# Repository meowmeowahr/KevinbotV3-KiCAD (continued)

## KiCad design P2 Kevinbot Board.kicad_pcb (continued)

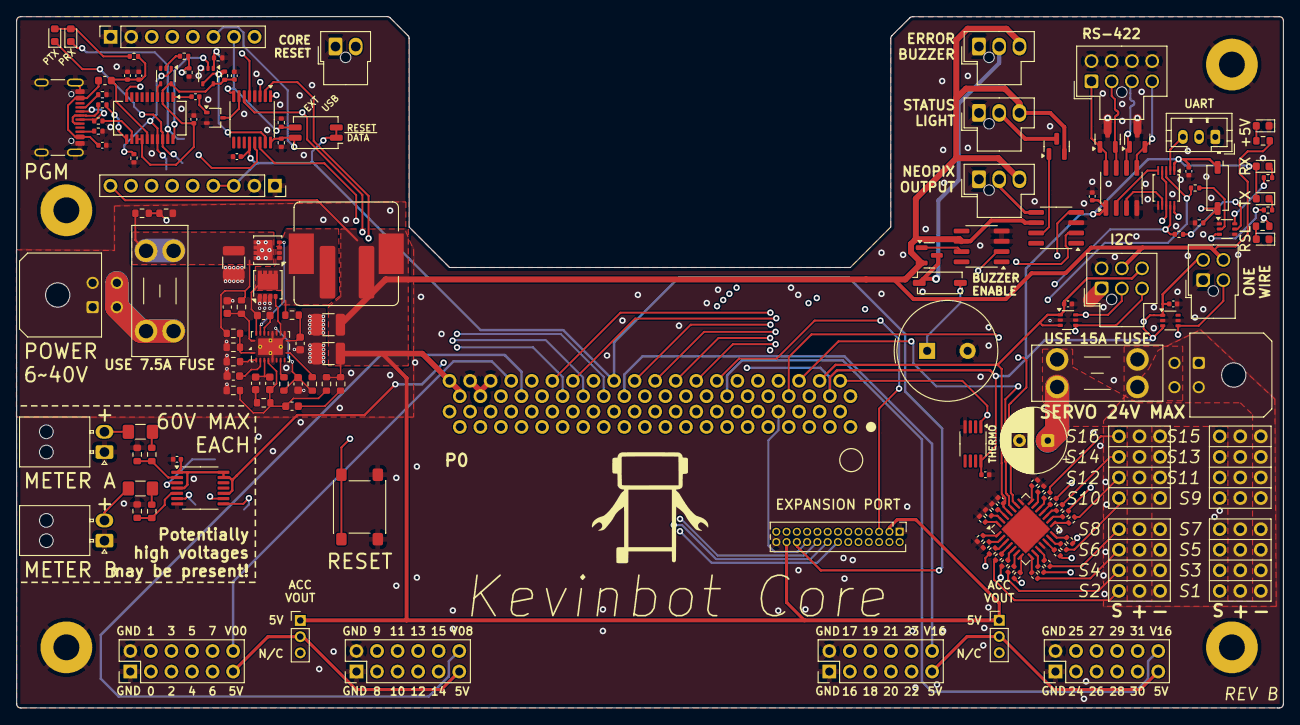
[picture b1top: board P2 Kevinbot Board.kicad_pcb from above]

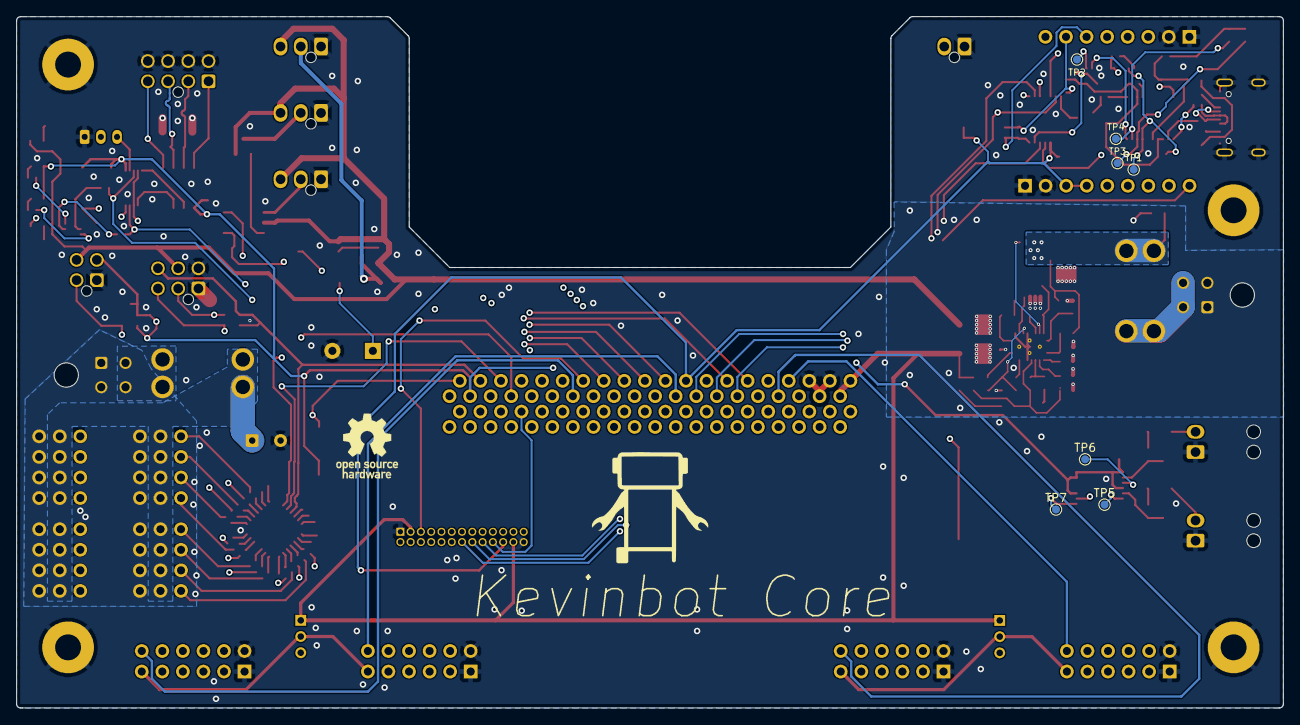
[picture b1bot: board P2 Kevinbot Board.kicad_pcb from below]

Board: 4 copper layers, 156.5 x 85.4 mm, 165 parts (8 on the bottom side), 192 nets.

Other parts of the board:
G1, G2: LOGO; Kevinbot15mm

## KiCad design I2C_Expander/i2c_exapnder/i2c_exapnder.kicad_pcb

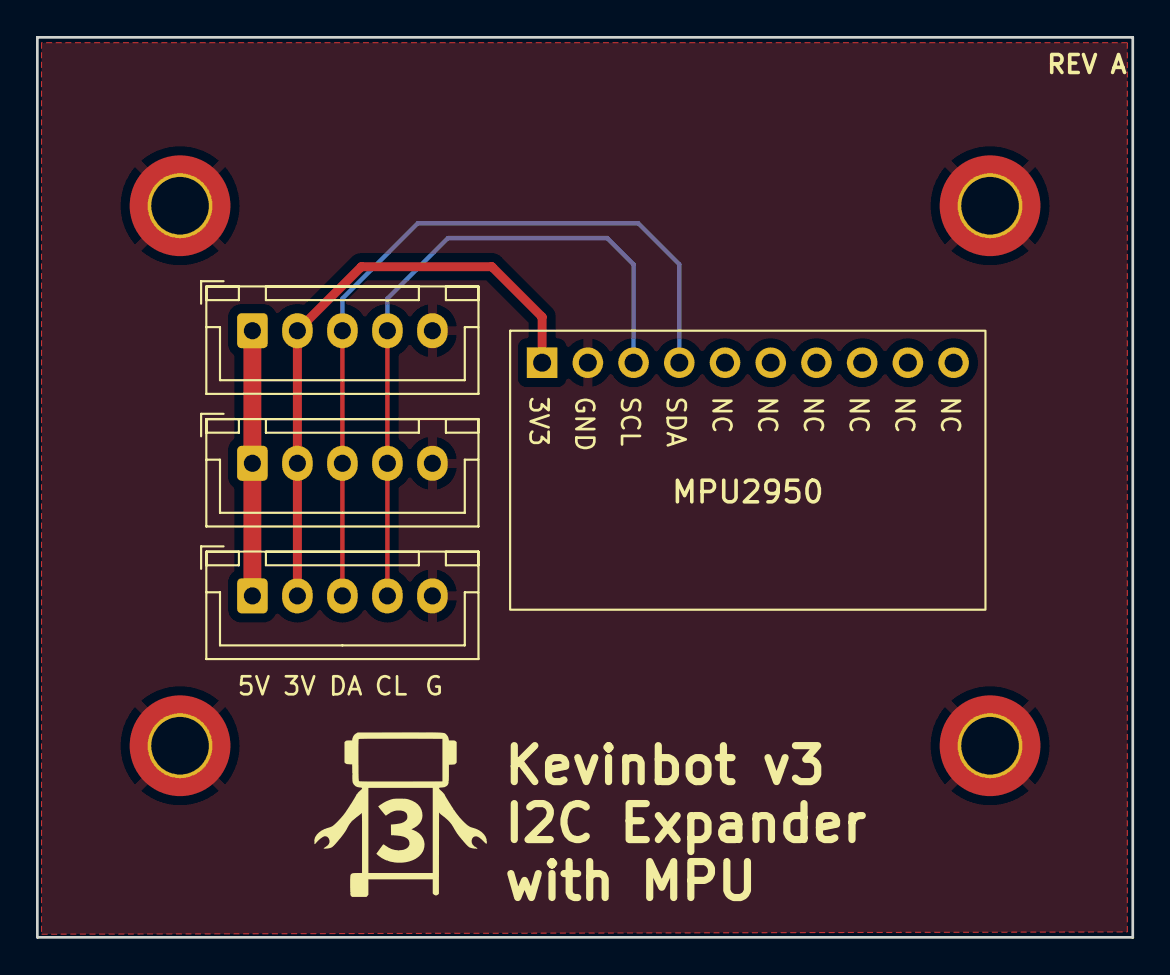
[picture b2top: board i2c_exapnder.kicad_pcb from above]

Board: 2 copper layers, 60.9 x 50.0 mm, 8 parts (0 on the bottom side), 5 nets.

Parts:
H1, H2, H3, H4: MountingHole_Pad; MountingHole_3.2mm_M3_DIN965_Pad_TopBottom
J1: Conn_01x10; MPU2950_Module
J2, J3, J4: Conn_01x05; JST_XH_B5B-XH-A_1x05_P2.50mm_Vertical

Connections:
+5V: J2.1, J3.1, J4.1
GND: H1.1, H2.1, H3.1, H4.1, J1.2, J2.5, J3.5, J4.5
SCL: J1.3, J2.4, J3.4, J4.4
SDA: J1.4, J2.3, J3.3, J4.3
V08: J1.1, J2.2, J3.2, J4.2

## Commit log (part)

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2023-02-17 Board cleanup
2023-02-26 Replace I2C headers with JST
2023-02-26 Fix DRC Warnings
2023-02-26 Move screw holes, move serial port to top
2023-02-26 Update gitignore
2023-02-26 Add I2C Expander with MPU2950
2023-02-26 Add 3D model to power jack
2023-02-26 Update Image
2023-02-27 Align I2C Expander screw holes
2023-02-27 Update Board Settings on I2C Expander
2023-03-06 Add logo and text to I2C Expander
2023-03-06 Add i2c expander image
2023-03-06 Add i2c expander image to README
2023-03-08 Cleanup
2023-05-07 Redesign for SMD and new pinmap
2023-05-10 Connector positioning
2023-05-20 Add motor driver conns, pinout changes
2023-05-20 More component placing
2023-05-20 Place buzzer
2023-05-20 Serial and EXT reset
2023-05-20 Add DS18B20
2023-05-20 Begin PCA placement
2023-05-20 PCA routing
2023-05-20 Finish PCA routing
2023-05-21 Remove WAGO 2606
2023-05-21 Remove I2C Expander
2023-05-21 Silkscreen updates
2023-05-21 Add Logo, cleanup
2024-06-21 Update kicad verison
2024-06-21 Re-arrange pca
2024-06-21 Make space for second servo connector row
2024-06-22 Make power led smd 0603
2024-06-22 Add 3v3 indicator
2024-06-22 Add servo power indicator
2024-06-22 Fix global labels
2024-06-22 Almost finish 2nd pca
2024-06-22 Finish 2nd pca
2024-06-22 Label servo 16..31
2024-06-22 Remove tmp files
2024-06-22 Begin adding pca
2024-06-23 Route 2nd pca
2024-06-23 Add int buzzer enable jumper
2024-06-23 Add ext buzzer fet and connector
2024-06-24 Add servo fuse, increase trace width
2024-06-24 Add new kevinbot logo
2024-06-24 Change pca section rects
2024-06-28 Change logo, led resistors
2024-06-28 Add logo footprints
2024-06-28 DRC fixes, add missing library, misc
2024-06-28 Add voltmeter polyfuses
2024-06-28 Add main fuse
2024-06-28 Logo changes
2024-06-29 Add mfr part numbers and datasheets to all
2024-06-29 Add rx/tx leds, schematic cleanup
2024-06-30 Add rsl
2024-06-30 Swap Serial pinout
2024-06-30 Swap rst and buz pinouts
2024-06-30 misc
2024-06-30 initial relocation of pca, re-order servo connectors
2024-06-30 Fix incorrect resistor part numbers
2024-06-30 Fix messed up 3d models
2024-06-30 Add servo filtering cap
2024-06-30 silkscreen changes
2024-06-30 Fix incorrect resistor value
2024-08-12 Use mosfet for internal buzzer
2024-08-12 Add ground test posts
2024-08-22 Remove incorrect p2 3d model
2024-08-23 P2 socket
2024-08-23 Silkscreen changes, DRC, make ground pin 1 for more conns
2024-08-24 README image update
2024-08-24 Add diagram for future docs
2024-08-24 .gitignore for drawio
2024-08-24 Writerside docs, test points for P33, P32
2024-08-25 Misc board changes
2024-08-25 Docs style changes
2024-08-26 Update board image
2024-08-26 Writerside changes, pcb expansion conn
2024-08-26 Update board diagram
2024-08-29 Board diagram descriptions
2024-08-29 Fix major mosfet wiring error
2024-08-29 Board revision
2024-08-29 Pin map blank page
2024-08-29 More board diagram descriptions
2024-08-29 Create LICENSE
2024-08-30 Better diagram images
2024-08-30 Diagram section 18 & 19
2024-08-30 docs: Diagram section 20
2024-08-30 docs: Diagram section 21 & 22
2024-08-30 docs: typo
2024-08-30 docs: Diagram section 23
2024-08-30 docs: Remove useless assets
2024-08-30 docs: Attempt to fix pdf issues
2024-08-30 docs: whoops
2024-08-30 docs: add missing files
2024-08-30 docs: download button
2024-08-30 docs: code of conduct
2024-08-31 Update issue templates
2024-08-31 exp fcc label
2024-08-31 gh actions
2024-08-31 Maybe fix gh actions
2024-08-31 Maybe fix gh actions 2
2024-09-03 First board render
2024-09-04 Via stitching, ground plane islanding
2024-09-04 Via stitching changes
2024-09-04 Vias, silkscreen changes
2024-09-04 docs: add board diagram sections 24~27
2024-09-04 docs: pin maps for exp header, p2-eval accessories
2024-09-05 docs: pin maps for board
2024-09-05 docs: gitignore
2024-09-05 docs: typos
2024-09-05 docs: add software info and sources
2024-09-05 docs: delete hardware toc element
2024-09-05 docs: rearrange toc
2024-09-05 Add Contributing.md
2024-09-05 docs: remove Hardware.md references
2024-09-05 Cleanup CONTRIBUTING.md
2024-09-05 Create DOCS-LICENSE
2024-09-05 docs: license information
2024-09-10 silkscreen, cleanup
2024-09-10 rev a silkscreen
2024-09-10 rev a writerside.cfg
2024-09-10 latest writerside.cfg
2024-09-10 Add help-versions.json
2024-09-10 docs: version switcher
2024-09-10 docs: web path
2024-09-14 Add open source certification mark
2024-09-14 Add oshw facts, oshwa cert mark to README
2024-09-14 Add oshw facts, oshwa cert mark to README
    (cherry picked from commit 0f2b0dd106c6840f650215bd934f5323cf529596)
2024-10-03 Add pcbway promo
2024-10-03 Add pcb images
2024-10-04 docs: pcbway promo
2024-10-04 docs: pcbway promo updates
2024-10-15 Use tc4427 for RSL OUT, first commit for RevB
2024-10-15 Swap servo power pins
2024-11-09 Add P2 Edge Slot 3d Model
2024-11-09 P2 Edge Slot credits
2024-12-24 fix buzzer fet
2024-12-24 init mkdocs, change dir structure
2024-12-24 migrate topics to mkdocs
2024-12-24 convert topic to mkdocs
2024-12-24 images to mkdocs
2024-12-24 no toc on index.md
2024-12-24 remove writerside
2024-12-24 Deployed 0eb3fd3 with MkDocs version: 1.6.1
2024-12-24 maybe fix images for gh pages
2024-12-24 Deployed be3661b with MkDocs version: 1.6.1
2024-12-24 fix image paths
2024-12-24 Deployed df5c291 with MkDocs version: 1.6.1
2024-12-24 rounded board corners
2025-01-10 Swap tx/rx conn labels
2025-03-25 Remove all components, redo board outline
2025-03-27 Mostly routed accessory headers
2025-03-28 Begin work on usbc programmer, misc
2025-03-28 USB caps
2025-04-02 Usb programme
2025-04-04 Buzzer
2025-04-04 Add leds, docs cleanup
2025-04-04 Deployed fbaeb60 to latest with MkDocs 1.6.1 and mike 2.1.3
2025-04-04 Add mike support
2025-04-04 Deployed e31c58c to latest with MkDocs 1.6.1 and mike 2.1.3
2025-04-04 testing for mike
2025-04-04 Set default version to latest with mike 2.1.3
2025-04-05 docs naming changes
2025-04-05 reset button
2025-04-05 Deployed 89df5ba to RevA with MkDocs 1.6.1 and mike 2.1.3
2025-04-05 Set default version to RevA with mike 2.1.3
2025-04-05 Maybe working mike in docs
2025-04-05 Deployed 3aff7af to RevA with MkDocs 1.6.1 and mike 2.1.3
2025-04-05 proper mike support
2025-04-05 Set title of latest to RevB with mike 2.1.3
2025-04-05 Remove latest for some weird mike issues
2025-04-05 Deployed 822861b to RevB with MkDocs 1.6.1 and mike 2.1.3
2025-04-05 Copied RevB to latest with mike 2.1.3
2025-04-05 docs: fresh start
2025-04-05 docs: add logo banner, pcb: reset text changes
2025-04-05 Deployed 1788869 to RevB with MkDocs 1.6.1 and mike 2.1.3
2025-04-05 docs: fix images again
2025-04-05 Deployed d23342b to RevB with MkDocs 1.6.1 and mike 2.1.3
2025-04-06 pcb, sch: add rs422 comm interface
2025-04-06 pcb, sch: add transciever decoupling cap, docs, wireviz: add rs422 wiring harness
2025-04-06 Deployed c36b5e8 to RevB with MkDocs 1.6.1 and mike 2.1.3
2025-04-06 docs: update index, combine learn
2025-04-06 pcb: relocate rs422
2025-04-06 pcb, sch: mounting holes
2025-04-06 docs: hopefully fix images again
2025-04-06 Deployed fa13dcf to RevB with MkDocs 1.6.1 and mike 2.1.3
2025-04-06 rs422, pcb: uart/rs422 mux
2025-04-09 docs: add wire info, psu: add connector, i2c: initial work, lots of changes
2025-04-09 cad: fix molex conn colors
2025-04-09 sch, pcb: update pn fields
2025-04-11 prog, pcb: test points
2025-04-11 prog, pgmmux, sch: hierarchical organization, prep for programmer mux
2025-04-11 docs; ftdi config
2025-04-11 pgmmux, sym: TS3A44159PWR symbol
2025-04-11 Deployed 3e56f31 to RevB with MkDocs 1.6.1 and mike 2.1.3
2025-04-11 pgmmux, pcb: add selector switch
2025-04-12 pgmmux, pcb: ext connectors
2025-04-12 readme: credits, banner
2025-04-12 flows: docs build with ibom
2025-04-12 flows: update for kicad 9.0, add glightbox
2025-04-12 flows: mike got removed for some reason
2025-04-12 Deployed 4a86c38 to RevB with MkDocs 1.6.1 and mike 2.1.3
2025-04-13 docs: add ibom, pcb, psu: fuse, pgmmux, pcb: 2.00mm headers -> 2.54
2025-04-13 Deployed f56fb00 to RevB with MkDocs 1.6.1 and mike 2.1.3
2025-04-13 pgmmux, pcb: mux bypass cap
2025-04-13 sym: TMUX1511, psu: add failsafe development
2025-04-13 psu, sch, pcb: voltmeters
2025-04-13 pcb: input ground plane
2025-04-13 pcb: p2 socket silkscreen
2025-04-13 docs: fixes
2025-04-13 Deployed da6eb10 to RevB with MkDocs 1.6.1 and mike 2.1.3
2025-04-13 flows: add Part Number to ibom, cleanup
2025-04-13 Deployed 50a8cd0 to RevB with MkDocs 1.6.1 and mike 2.1.3
2025-04-13 sch, pcb: add part numbers
2025-04-13 Deployed 79cb145 to RevB with MkDocs 1.6.1 and mike 2.1.3
2025-04-13 flows: font install
2025-04-13 Deployed ad5d70f to RevB with MkDocs 1.6.1 and mike 2.1.3
2025-04-13 owx, pcb: add one wire
2025-04-13 Deployed 96599b8 to RevB with MkDocs 1.6.1 and mike 2.1.3
2025-04-13 docs: electrical specs, ibom changes
2025-04-13 Deployed 0500b8d to RevB with MkDocs 1.6.1 and mike 2.1.3
2025-04-13 psu, pcb: 5v pwr led
2025-04-13 Deployed 9c8047b to RevB with MkDocs 1.6.1 and mike 2.1.3
2025-04-13 pcb: drc
2025-04-13 vscode: spell check
2025-04-13 Deployed a833a7d to RevB with MkDocs 1.6.1 and mike 2.1.3
2025-04-14 i2c, servo, pcb: pca9685 servo, pcb, rs422: leds
2025-04-14 Deployed e2dba7f to RevB with MkDocs 1.6.1 and mike 2.1.3
2025-04-14 buzzout, pcb: use dip switch for buzzer enable, pcb: servo output pin labels
2025-04-14 Deployed fc4d7da to RevB with MkDocs 1.6.1 and mike 2.1.3
2025-04-14 docs: prune old images, pcb: cleanup
2025-04-14 Deployed a577066 to RevB with MkDocs 1.6.1 and mike 2.1.3
2025-04-15 rs422, led, pcbs: status leds, readme: add image
2025-04-15 Deployed d323831 to RevB with MkDocs 1.6.1 and mike 2.1.3
2025-04-15 docs: update specs, add board image
2025-04-16 docs: revision comparison updates
2025-04-16 Deployed 2122864 to RevB with MkDocs 1.6.1 and mike 2.1.3
2025-04-23 buck, pcb, misc: add buck psu
2025-04-23 Deployed 3c14c00 to RevB with MkDocs 1.6.1 and mike 2.1.3
2025-04-23 pcb, buck: cleanup, add 7070 inductor DNP footprint
2025-04-23 docs: update media, cleanup index
2025-04-23 Deployed 0ed854b to RevB with MkDocs 1.6.1 and mike 2.1.3
2025-04-23 sch: erc
2025-04-24 sch, pcb: exp header
2025-04-24 Deployed cd7044e to RevB with MkDocs 1.6.1 and mike 2.1.3
2025-04-25 docs: image gallery
2025-04-25 Deployed 50d71f9 to RevB with MkDocs 1.6.1 and mike 2.1.3
2025-05-08 Servo filtering, cleanup
2025-05-08 Deployed 8644b83 to RevB with MkDocs 1.6.1 and mike 2.1.3
2025-05-08 Via stitching
2025-05-08 Part numbers
2025-05-08 Deployed 72723c1 to RevB with MkDocs 1.6.1 and mike 2.1.3
2025-05-11 Set default version to RevB with mike 2.1.3
2025-05-11 docs: board diagram
2025-05-11 Deployed d44c8c3 to RevB with MkDocs 1.6.1 and mike 2.1.3
2025-07-11 Update to latest footprints, cleanup
2025-07-11 Deployed 2113f7c to RevB with MkDocs 1.6.1 and mike 2.1.3
2025-07-11 Deployed ac3e49a to RevB with MkDocs 1.6.1 and mike 2.1.3
2025-07-11 part number fix
2025-07-11 Deployed 0bca70d to RevB with MkDocs 1.6.1 and mike 2.1.3
2025-07-16 update cert mark, still need to add to pcb
2025-07-16 Deployed 613ca9c to RevB with MkDocs 1.6.1 and mike 2.1.3
